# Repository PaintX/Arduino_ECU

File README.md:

# Arduino_ECU
Create PCB for Speeduino ECU in SMD

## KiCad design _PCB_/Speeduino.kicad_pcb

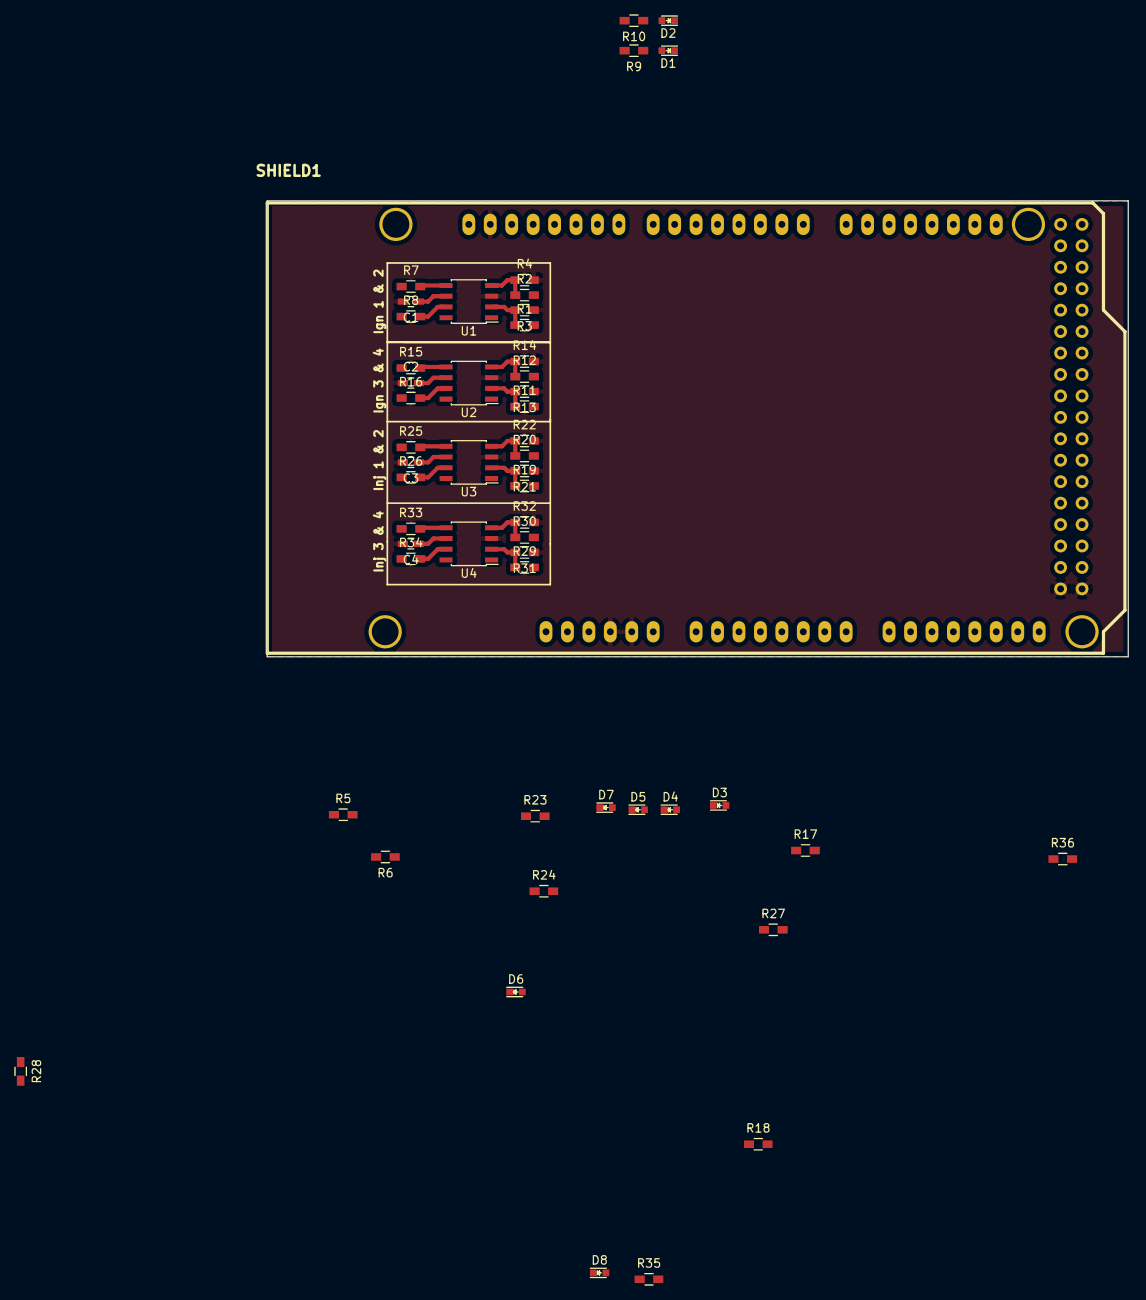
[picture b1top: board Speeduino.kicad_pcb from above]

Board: 2 copper layers, 102.0 x 54.0 mm, 53 parts (0 on the bottom side), 45 nets.

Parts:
C1, C2, C3, C4: C; C_0603_HandSoldering
D1, D2, D3, D4, D5, D6, D7, D8: LED; LED_0603
R1, R2, R11, R12, R19, R20, R29, R30: 1K; R_0603_HandSoldering
R3, R4, R13, R14, R21, R22, R31, R32: 100K; R_0603_HandSoldering
R5, R6, R23, R24: 0; R_0603_HandSoldering
R7, R8, R9, R10, R15, R16, R17, R18, R25, R26, R27, R28, R33, R34, R35, R36: R; R_0603_HandSoldering
SHIELD1: ARDUINO_MEGA_SHIELD; ARDUINO MEGA SHIELD
U1, U2, U3, U4: TC4424AVOA; SOIC-8_3.9x4.9mm_Pitch1.27mm

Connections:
+5V: R5.2, R23.2
+12V: R6.1, R24.1
GND: C1.2, C2.1, C3.2, C4.2, D1.1, D2.1, D3.1, D4.1, D5.1, D6.1, D7.1, D8.1, R3.1, R4.2, R13.1, R14.2, R21.1, R22.2, R31.1, R32.2, SHIELD1.GND1, SHIELD1.GND2, SHIELD1.GND3, SHIELD1.GND4, SHIELD1.GND5, U1.3, U2.3, U3.3, U4.3
IGN1_CPU_D40: R1.2, SHIELD1.40
IGN2_CPU_D38: R2.2, SHIELD1.38
IGN3_CPU_D52: R11.2, SHIELD1.52
IGN4_CPU_D50: R12.2, SHIELD1.50
IGN-3-OUT: R16.1, R18.2
IGN-4-OUT: R15.1, R17.2
ING-1-OUT: R8.1, R10.2
ING-2-OUT: R7.1, R9.2
INJ1_CPU_D8: R19.2, SHIELD1.8
INJ2_CPU_D9: R20.2, SHIELD1.9
INJ3_CPU_D10: R29.2, SHIELD1.10
INJ4_CPU_D11: R30.2, SHIELD1.11
INJ-1-OUT: R26.1, R28.2
INJ-2-OUT: R25.1, R27.2
INJ-3-OUT: R34.1, R36.2
INJ-4-OUT: R33.1, R35.2
unnamed: D1.2, R9.1
unnamed: D2.2, R10.1
unnamed: D3.2, R17.1
unnamed: D4.2, R18.1
unnamed: D5.2, R27.1
unnamed: D6.2, R28.1
unnamed: D7.2, R35.1
unnamed: D8.2, R36.1
unnamed: R1.1, R3.2, U1.2
unnamed: R2.1, R4.1, U1.4
unnamed: R7.2, U1.5
unnamed: R8.2, U1.7
unnamed: R11.1, R13.2, U2.2
unnamed: R12.1, R14.1, U2.4
unnamed: R15.2, U2.5
unnamed: R16.2, U2.7
unnamed: R19.1, R21.2, U3.2
unnamed: R20.1, R22.1, U3.4
unnamed: R25.2, U3.5
unnamed: R26.2, U3.7
unnamed: R29.1, R31.2, U4.2
unnamed: R30.1, R32.1, U4.4
unnamed: R33.2, U4.5
unnamed: R34.2, U4.7
VCC_IGNITION: C1.1, C2.2, R5.1, R6.2, U1.6, U2.6
VCC_INJECTOR: C3.1, C4.1, R23.1, R24.2, U3.6, U4.6

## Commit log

2016-01-14 - ajout fichier
2016-01-14 - debut du dev
2016-01-15 - ajout quelques fichiers
2016-01-15 - avance du projet,
2016-01-15 - ajout fichiers
2016-01-15 - supression fichiers
2016-01-15 - ajout fichier de test via codeblock
2016-01-15 - suppression fichier .gitignore
2016-01-15 - ajout protocol tunerstudio
2016-01-15 - integration tunerstudio
2016-01-15 fonctionne avec tunerstudio !!!!
2016-01-17 - ajout de fichiers
2016-01-17 - TunerStudio is OK !!!!!
2016-01-18 ajout fichier d'interpolation
2016-01-18 - oubli d'un fichier
2016-01-18 - ajout de fonctions - affichage du degré d'avance sur tunerstudio
2016-01-18 - fichier excel pour simulation calcul
2016-01-19 ajout de fichier
2016-01-19 -simplification de l'architecture des fichiers -possibilité de debugguer via codeblock et gcc
2016-01-19 mise a jours des fichiers
2016-01-19 - fonctionne sur arduino sauf table d'avance * debut integration simulation via codeblock
2016-01-19 ajout gitignore
2016-01-20 - ajout gestion xml pour simulation via pc
2016-01-20 - fonctionne en simulation - ajout d'un logo sur le lcd pour dire que l'on est connecter a tunerstudio - l'avance fonctionne
2016-01-20 - ajout calcul gestion dwell - ajout calucl gestion offset en degrée
2016-02-03 - creation debut PCB basé sur speeduino
2016-02-03 - suppression
2016-02-03 - add librarie
2016-02-03 - ajout version de speeduino pour faire le devloppement
2016-02-03 - modification readme
2016-02-03 ajout d'empreinte ajoute de la sheet injecteur
2016-02-03 - ajout schematic 4 injecteurs
2016-02-05 - ajout footprint to223
2016-02-05 - ajout BSP149
2016-02-08 changement de transistor sur les sorties
2016-02-08 - modification majeur sur les sortie injecteur . - pas d'étage de puissance sur les sorties injecteurs
2016-02-08 modification sortie injecteur
2016-02-10 ajout fichiers
2016-02-10 routage des sorties de semi puissance !!
